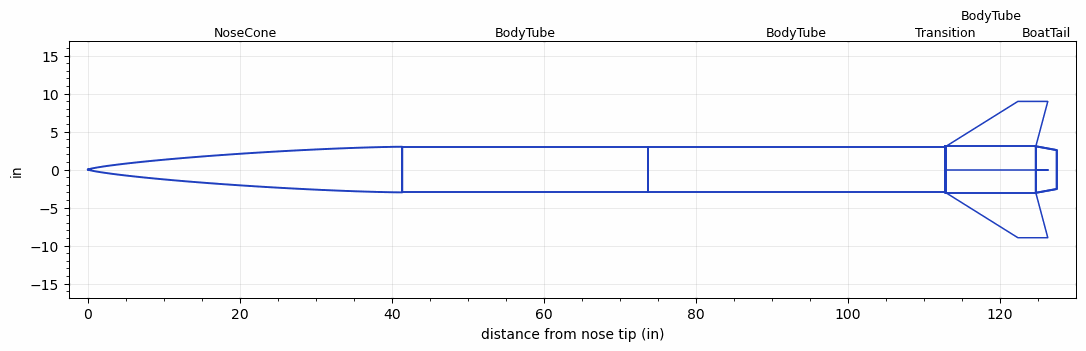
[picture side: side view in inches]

<RASAeroDocument>
 <FileVersion>2</FileVersion>
 <RocketDesign>
  <NoseCone>
   <Length>41.3386</Length>
   <Diameter>6</Diameter>
   <Shape>Von Karman Ogive</Shape>
   <Location>0</Location>
  </NoseCone>
  <BodyTube>
   <Length>32.3622</Length>
   <Diameter>6</Diameter>
   <Location>41.3386</Location>
   <Protuberance>
    <StreamlinedNoBaseDrag>1.608</StreamlinedNoBaseDrag>
    <StreamlinedWithBaseDrag>0</StreamlinedWithBaseDrag>
    <InclinedPlate1Angle>0</InclinedPlate1Angle>
    <InclinedPlate1FrontalArea>0</InclinedPlate1FrontalArea>
    <InclinedPlate2Angle>0</InclinedPlate2Angle>
    <InclinedPlate2FrontalArea>0</InclinedPlate2FrontalArea>
   </Protuberance>
  </BodyTube>
  <BodyTube>
   <Length>38.9763</Length>
   <Diameter>6</Diameter>
   <Location>73.70081</Location>
  </BodyTube>
  <Transition>
   <Length>0.1985</Length>
   <Diameter>6.1181</Diameter>
   <Location>112.6771</Location>
   <RearDiameter>6.1181</RearDiameter>
  </Transition>
  <BodyTube>
   <Length>11.811</Length>
   <Diameter>6.1181</Diameter>
   <Location>112.8756</Location>
   <BoattailLength>2.7559</BoattailLength>
   <BoattailRearDiameter>5.1181</BoattailRearDiameter>
   <Fin>
    <Count>4</Count>
    <Chord>11.811</Chord>
    <Span>5.906</Span>
    <SweepDistance>9.449</SweepDistance>
    <TipChord>3.937</TipChord>
    <Thickness>0.188</Thickness>
    <LERadius>0.04</LERadius>
    <Location>11.811</Location>
    <AirfoilSection>Hexagonal</AirfoilSection>
    <FX1>0.35</FX1>
    <FX3>0.35</FX3>
   </Fin>
   <Protuberance>
    <StreamlinedNoBaseDrag>0.575</StreamlinedNoBaseDrag>
    <StreamlinedWithBaseDrag>0</StreamlinedWithBaseDrag>
    <InclinedPlate1Angle>0</InclinedPlate1Angle>
    <InclinedPlate1FrontalArea>0</InclinedPlate1FrontalArea>
    <InclinedPlate2Angle>0</InclinedPlate2Angle>
    <InclinedPlate2FrontalArea>0</InclinedPlate2FrontalArea>
   </Protuberance>
  </BodyTube>
  <BoatTail>
   <Length>2.7559</Length>
   <Diameter>6.1181</Diameter>
   <RearDiameter>5.1181</RearDiameter>
   <Location>124.6866</Location>
  </BoatTail>
  <Surface>Camouflage Paint</Surface>
  <ModifiedBarrowman>True</ModifiedBarrowman>
  <Turbulence>True</Turbulence>
  <UseBooster1>False</UseBooster1>
  <UseBooster2>False</UseBooster2>
  <Comments>C</Comments>
 </RocketDesign>
 <LaunchSite>
  <Altitude>2940</Altitude>
  <Pressure>29.8</Pressure>
  <RodAngle>6</RodAngle>
  <RodLength>13</RodLength>
  <Temperature>103</Temperature>
  <WindSpeed>3</WindSpeed>
 </LaunchSite>
 <Recovery>
  <Altitude1>0</Altitude1>
  <Altitude2>1394.36</Altitude2>
  <DeviceType1>Parachute</DeviceType1>
  <DeviceType2>Parachute</DeviceType2>
  <Event1>True</Event1>
  <Event2>True</Event2>
  <Size1>39.37</Size1>
  <Size2>145.6693</Size2>
  <EventType1>Apogee</EventType1>
  <EventType2>Altitude</EventType2>
  <CD1>0.9</CD1>
  <CD2>1.2</CD2>
 </Recovery>
 <SimulationList>
  <Simulation>
   <SustainerEngine>ASTROMFINAL  (KOSMOS)</SustainerEngine>
   <SustainerLaunchWt>102.51</SustainerLaunchWt>
   <SustainerNozzleDiameter>3.5</SustainerNozzleDiameter>
   <SustainerCG>85</SustainerCG>
   <SustainerIgnitionDelay>0</SustainerIgnitionDelay>
   <Booster1SeparationDelay>0</Booster1SeparationDelay>
   <Booster1IgnitionDelay>0</Booster1IgnitionDelay>
   <IncludeBooster1>False</IncludeBooster1>
   <Booster2Delay>0</Booster2Delay>
   <IncludeBooster2>False</IncludeBooster2>
   <TimetoApogee>42.04895</TimetoApogee>
   <MaxAltitude>30255.79</MaxAltitude>
   <MaxVelocity>1621.356</MaxVelocity>
  </Simulation>
 </SimulationList>
</RASAeroDocument>
